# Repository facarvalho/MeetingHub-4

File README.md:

# MeetingHub-4

Analog audio hub for 4 laptops — monitor all four at once (per-source + master
volume), speak on one at a time with a physical mic selector, use one ordinary
TRRS headset, install nothing on any laptop. 100 % analog: no USB audio, no
Bluetooth, no firmware.

## Versions

| | [`v1/`](v1/) — fabricated | [`v2/`](v2/) — respin | [`v3/`](v3/) — mic selector only |
|---|---|---|---|
| Scope | monitor 4 + talk on 1 | monitor 4 + talk on 1 | **talk on 1 only** (audio → external mixer + Y-cables) |
| PCB | 4-layer, 265 × 160 mm | **2-layer**, 192 × 156 mm | **4-layer** (GND + 5 V planes), ~**106 × 86 mm** |
| Assembly | 3 SMD groups + jack SMD pads | **100 % through-hole** | **100 % through-hole** (vertical passives) |
| Mic selector | latching push-locks driving relays | **on-board one-hot latch** (CD4043B + diode matrix + 2N7000), momentary buttons, power-on = muted | **same one-hot latch**; relay NC pulled to GND via 2k2 so a de-selected notebook still reads "mic present" |
| Audio path | mixer + headphone amp + pots + VBIAS | mixer + headphone amp + pots + VBIAS (LM358) | **none** |
| Status | fabricated (JLCPCB lot `W2026080810364558`); first article found 3 schematic bugs | routed, DRC-clean; **not yet fabricated** | routed, DRC-clean, sim 22/22; **not yet fabricated** — open in KiCad, run native ERC/DRC first |

Each folder is **self-contained** (its own `hardware/`, `docs/`, scripts, BOM,
gerbers). Start with the `README.md` / `CLAUDE.md` inside the folder you want.

- **v1 history & rework:** `v1/README.md`, `v1/docs/REWORK-001…004`,
  `v1/docs/Architecture/SCH-010-OneHotMicSelector.md` (the selector design that
  became v2).
- **v2 design & build:** `v2/README.md`, `v2/docs/v2-DESIGN.md`,
  `v2/docs/v1-vs-v2.md`, `v2/CHANGELOG.md`.
- **v3 (mic selector only):** `v3/README.md`, `v3/docs/v3-DESIGN.md`,
  `v3/CHANGELOG.md`.

## License

Commercial license with usage royalty — see [LICENSE.md](LICENSE.md). Not open
hardware; commercial use requires a paid license. No document here is legal
advice.

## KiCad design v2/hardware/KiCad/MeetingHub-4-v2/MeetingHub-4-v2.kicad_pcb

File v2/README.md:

# MeetingHub-4 v2

Analog audio hub for 4 laptops — monitor all four at once, talk on one — with a
single TRRS headset. No drivers, no firmware, 100 % analog.

**v2 = a clean respin of the design:** 2-layer PCB, every part through-hole and
hand-solderable, the mic selector's exclusive "one-hot" logic now on the board
itself, no mute button, and all three bugs from the first fabricated batch fixed.

| | |
|---|---|
| **Status** | Schematic complete, PCB **fully auto-routed** (2 layers, rev-8: 850 seg / 30 vias), DRC clean apart from known cosmetic items. Not yet fabricated. Open in KiCad to tidy silkscreen and run native DRC before ordering. |
| **PCB** | 2 layers, **192 × 156 mm**, R6 rounded corners, 6× M3, GND pour both sides. |
| **Enclosure** | top + bottom acrylic only, sides open (no front panel). |
| **Supply** | USB-C, 5 V only (no regulator, no boost). |
| **BOM** | 117 parts, 100 % THT — every LCSC code in stock with a ready footprint (rev-8 audit). PCBA: [`BOM-PCBA`](hardware/BOM/BOM-PCBA-MeetingHub-4-v2.csv) · upload [`BOM-JLC`](hardware/BOM/BOM-JLC-MeetingHub-4-v2.csv) for assembly · [component photos + links](docs/components.html). |
| **Fab files** | [`hardware/Gerbers/MeetingHub-4-v2-Gerbers.zip`](hardware/Gerbers/) — order as **2-layer**, 1.6 mm, HASL is fine. `…-CPL.csv` has the per-footprint rotation fixes for JLC assembly. |

## How it works

- **Monitor:** each laptop plugs into J2–J5 (TRRS). Its L/R audio goes through a
  DC-block, a per-laptop volume pot (RV1–RV4), a 4-input stereo summing mixer
  (U1 NJM4580), a master volume (RV5), a headphone amp (U2 NJM4556A), out to the
  headset J6. All four are always summed.
- **Talk:** the headset mic (J6 sleeve) is routed by one of four signal relays
  (K1–K4) to exactly one laptop's mic pin.
- **Selecting:** four momentary buttons (SW2–SW5). Press NB2 → laptop 2's relay
  latches on and any other releases (KVM-style). The latch is a CD4043B
  (U4) + diode matrix + 4× 2N7000 coil drivers (the SELECT_LOGIC sheet).
- **Mute:** there is no mute button. **At power-on nothing is latched → the mic
  reaches no laptop → muted.** During a call, mute in the meeting app, or hold
  any two select buttons.
- **Volume direction:** clockwise = louder on every pot (verified against the
  Alps terminal convention — see the design doc).

## Reading order

1. [`docs/v2-DESIGN.md`](docs/v2-DESIGN.md) — what changed from v1, the
   one-hot logic, and the 3-pass circuit review (4 laptops connected).
2. [`CLAUDE.md`](CLAUDE.md) — repo layout and how the files were generated.
3. [`CHANGELOG.md`](CHANGELOG.md).
4. The KiCad project in [`hardware/KiCad/MeetingHub-4-v2/`](hardware/KiCad/MeetingHub-4-v2/).

The v1/v2 design and its hand-rework guides are in the parent folder and are
**not** part of v2.

## License

Inherits the parent project's commercial license with usage royalty — see
`../LICENSE.md`. Not open-source hardware.

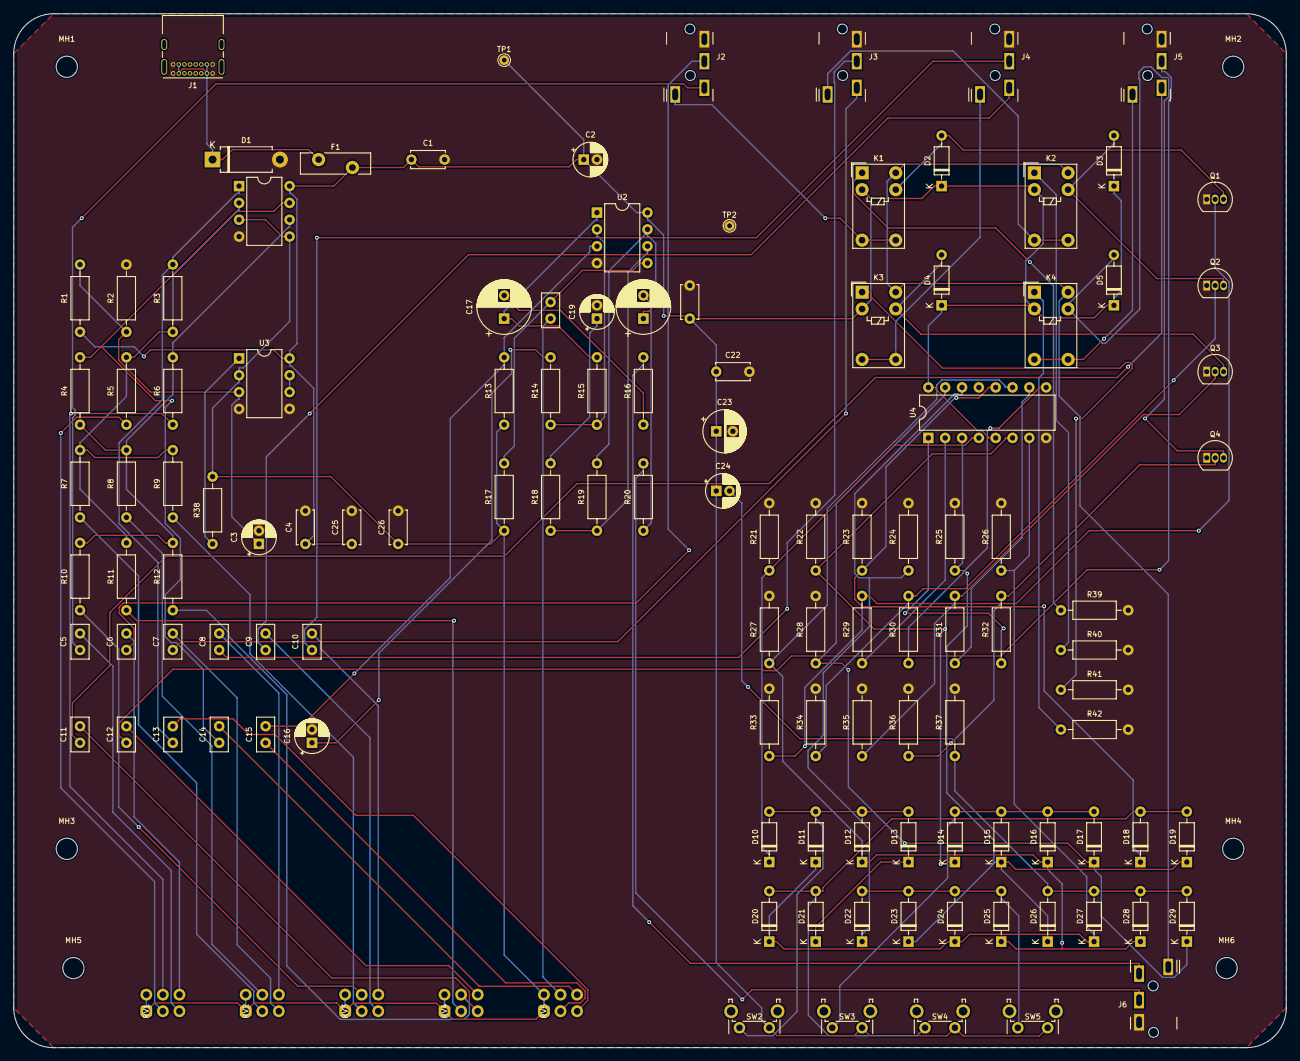
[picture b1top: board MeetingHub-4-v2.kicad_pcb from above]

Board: 2 copper layers, 192.0 x 156.0 mm, 129 parts (0 on the bottom side), 85 nets.

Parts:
C1, C4, C21, C22, C25, C26: C_Disc_D5.0mm_W2.5mm_P5.00mm
C2, C3, C16, C19, C24: CP_Radial_D5.0mm_P2.00mm
C5, C6, C7, C8, C9, C10, C11, C12, C13, C14, C15, C18: C_Disc_D5.0mm_W2.5mm_P2.50mm
C17, C20: CP_Radial_D8.0mm_P3.50mm
C23: CP_Radial_D6.3mm_P2.50mm
D1: D_DO-15_P10.16mm_Horizontal
D2, D3, D4, D5, D10, D11, D12, D13, D14, D15, D16, D17, D18, D19, D20, D21, D22, D23, D24, D25, D26, D27, D28, D29: D_DO-35_SOD27_P7.62mm_Horizontal
F1: Fuse_Bourns_MF-RG500
J1: USB_C_Receptacle_GCT_USB4085
J2, J3, J4, J5, J6: Jack_3.5mm_PJ-3200B-4A_Horizontal
K1, K2, K3, K4: Relay_SPDT_Omron_G5V-1
MH1, MH2, MH3, MH4, MH5, MH6: MountingHole_3.2mm_M3
Q1, Q2, Q3, Q4: TO-92_Inline
R1, R2, R3, R4, R5, R6, R7, R8, R9, R10, R11, R12, R13, R14, R15, R16, R17, R18, R19, R20, R21, R22, R23, R24, R25, R26, R27, R28, R29, R30, R31, R32, R33, R34, R35, R36, R37, R38, R39, R40, R41, R42: R_Axial_DIN0207_L6.3mm_D2.5mm_P10.16mm_Horizontal
RV1, RV2, RV3, RV4, RV5: Potentiometer_Alps_RK097_Dual_Horizontal
SW2, SW3, SW4, SW5: SW_Tactile_SPST_Angled_PTS645Vx39-2LFS
TP1, TP2: TestPoint_THTPad_D1.5mm_Drill0.7mm
U1, U2, U3: DIP-8_W7.62mm
U4: DIP-16_W7.62mm

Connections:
+5V_AUDIO: C1.1, C2.1, C4.1, C21.1, C22.1, C23.1, C24.1, C25.1, D2.1, D3.1, D4.1, D5.1, F1.2, K1.2, K2.2, K3.2, K4.2, R1.1, SW2.1, SW3.1, SW4.1, SW5.1, TP1.1, U1.8, U2.8, U3.8, U4.5, U4.16
/MIC_SWITCHING/NCHLD1: K1.1, R39.1
/MIC_SWITCHING/NCHLD2: K2.1, R40.1
/MIC_SWITCHING/NCHLD3: K3.1, R41.1
/MIC_SWITCHING/NCHLD4: K4.1, R42.1
/SELECT_LOGIC/BTN1: D10.2, D11.2, D12.2, D13.2, SW2.2
/SELECT_LOGIC/BTN2: D14.2, D15.2, D16.2, D17.2, SW3.2
/SELECT_LOGIC/BTN3: D18.2, D19.2, D20.2, D21.2, SW4.2
/SELECT_LOGIC/BTN4: D22.2, D23.2, D24.2, D25.2, SW5.2
/SELECT_LOGIC/GATE1: Q1.2, R29.2, R33.1
/SELECT_LOGIC/GATE2: Q2.2, R30.2, R34.1
/SELECT_LOGIC/GATE3: Q3.2, R31.2, R35.1
/SELECT_LOGIC/GATE4: Q4.2, R32.2, R36.1
/SELECT_LOGIC/PORN: C24.2, D26.2, D27.2, D28.2, D29.2, R37.1
/SELECT_LOGIC/QO1: R29.1, U4.2
/SELECT_LOGIC/QO2: R30.1, U4.9
/SELECT_LOGIC/QO3: R31.1, U4.10
/SELECT_LOGIC/QO4: R32.1, U4.1
/SELECT_LOGIC/RST1: D15.1, D19.1, D23.1, D26.1, R25.1, U4.3
/SELECT_LOGIC/RST2: D11.1, D20.1, D24.1, D27.1, R26.1, U4.7
/SELECT_LOGIC/RST3: D12.1, D16.1, D25.1, D28.1, R27.1, U4.11
/SELECT_LOGIC/RST4: D13.1, D17.1, D21.1, D29.1, R28.1, U4.15
/SELECT_LOGIC/SET1: D10.1, R21.1, U4.4
/SELECT_LOGIC/SET2: D14.1, R22.1, U4.6
/SELECT_LOGIC/SET3: D18.1, R23.1, U4.12
/SELECT_LOGIC/SET4: D22.1, R24.1, U4.14
/SELECT_LOGIC/U3B_FB: U3.6, U3.7
/SELECT_LOGIC/VB_OUT: R38.1, U3.1
COIL1: D2.2, K1.9, Q1.3
COIL2: D3.2, K2.9, Q2.3
COIL3: D4.2, K3.9, Q3.3
COIL4: D5.2, K4.9, Q4.3
GND: C1.2, C2.2, C3.2, C4.2, C16.2, C19.2, C21.2, C22.2, C23.2, C25.2, C26.2, D1.2, J1.A1, J1.A12, J1.B1, J1.B12, J2.R2, J3.R2, J4.R2, J5.R2, J6.R2, Q1.1, Q2.1, Q3.1, Q4.1, R2.2, R21.2, R22.2, R23.2, R24.2, R25.2, R26.2, R27.2, R28.2, R33.2, R34.2, R35.2, R36.2, R37.2, R39.2, R40.2, R41.2, R42.2, TP2.1, U1.4, U2.4, U3.4, U3.5, U4.8
HEADSET_MIC: J6.S, K1.10, K2.10, K3.10, K4.10
MIX_L: C15.1, RV5.2
MIX_R: C18.1, RV5.5
NB1_L: C5.1, J2.T
NB1_MIC: J2.S, K1.5, K1.6
NB1_R: C6.1, J2.R1
NB2_L: C7.1, J3.T
NB2_MIC: J3.S, K2.5, K2.6
NB2_R: C8.1, J3.R1
NB3_L: C9.1, J4.T
NB3_MIC: J4.S, K3.5, K3.6
NB3_R: C10.1, J4.R1
NB4_L: C11.1, J5.T
NB4_MIC: J5.S, K4.5, K4.6
NB4_R: C12.1, J5.R1
unnamed: C5.2, RV1.3
unnamed: C6.2, RV1.6
unnamed: C7.2, RV2.3
unnamed: C8.2, RV2.6
unnamed: C9.2, RV3.3
unnamed: C10.2, RV3.6
unnamed: C11.2, RV4.3
unnamed: C12.2, RV4.6
unnamed: C13.1, R3.2, U1.1
unnamed: C13.2, RV5.3
unnamed: C14.1, R4.2, U1.7
unnamed: C14.2, RV5.6
unnamed: C16.1, R14.2
unnamed: C17.1, R15.2, U2.1
unnamed: C17.2, R16.1
unnamed: C19.1, R18.2
unnamed: C20.1, R19.2, U2.7
unnamed: C20.2, R20.1
unnamed: D1.1, F1.1, J1.A4, J1.A9, J1.B4, J1.B9
unnamed: J6.R1, R20.2
unnamed: J6.T, R16.2
unnamed: R5.1, RV1.2
unnamed: R6.1, RV1.5
unnamed: R7.1, RV2.2
unnamed: R8.1, RV2.5
unnamed: R9.1, RV3.2
unnamed: R10.1, RV3.5
unnamed: R11.1, RV4.2
unnamed: R12.1, RV4.5
unnamed: R3.1, R5.2, R7.2, R9.2, R11.2, U1.2
unnamed: R4.1, R6.2, R8.2, R10.2, R12.2, U1.6
unnamed: C15.2, R13.2, U2.3
unnamed: R14.1, R15.1, U2.2
unnamed: C18.2, R17.2, U2.5
unnamed: R18.1, R19.1, U2.6
VBIAS: C26.1, R13.1, R17.1, R38.2, RV1.1, RV1.4, RV2.1, RV2.4, RV3.1, RV3.4, RV4.1, RV4.4, RV5.1, RV5.4, U1.3, U1.5, U3.2
VBIAS_REF: C3.1, R1.2, R2.1, U3.3

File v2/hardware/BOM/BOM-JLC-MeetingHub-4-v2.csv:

Comment,Designator,Footprint,JLCPCB Part #
K104K15X7RF5TH5,"C1, C4, C21, C22, C25",C_Disc_D5.0mm_P5.00mm,C2167231
KM106M016D11RR0VH2FP0,"C2, C3, C16, C19, C24",CP_Radial_D5.0mm_P2.00mm,C43799
K105K20X7RF5TH5,"C5, C6, C7, C8, C9, C10, C11, C12, C13, C14, C15, C18, C26",C_Disc_D5.0mm_P2.50mm,C2167638
KM227M035F12RR0VH2FP0,"C17, C20",CP_Radial_D8.0mm_P3.50mm,C2063
NXA16V100M5X11,C23,CP_Radial_D6.3mm_P2.50mm,C346930
P6KE6.8A,D1,D_DO-15_P10.16mm,C152132
1N4148,"D2, D3, D4, D5, D10, D11, D12, D13, D14, D15, D16, D17, D18, D19, D20, D21, D22, D23, D24, D25, D26, D27, D28, D29",D_DO-35_P7.62mm,C402212
RXEF050,F1,Fuse_Bourns_MF-RG500,C76399
USB4085-GF-A,J1,USB_C_Receptacle_GCT_USB4085,C7095263
PJ-3200B-4A,"J2, J3, J4, J5, J6",Jack_3.5mm_PJ-3200B-4A_Horizontal,C136687
G5V-1-DC5,"K1, K2, K3, K4",Relay_SPDT_Omron_G5V-1,C28695
2N7000,"Q1, Q2, Q3, Q4",TO-92_Inline,C9114
CFR-25JB-52-10K,"R1, R2, R5, R6, R7, R8, R9, R10, R11, R12",R_Axial_DIN0207_P10.16mm,C5618323
MF1/4W-3.3K-1%,"R3, R4",R_Axial_DIN0207_P10.16mm,C119335
MFR-25FBF52-100K,"R13, R17, R21, R22, R23, R24, R25, R26, R27, R28, R33, R34, R35, R36, R37",R_Axial_DIN0207_P10.16mm,C1364475
CF1/4W-1KR-J,"R14, R15, R18, R19, R29, R30, R31, R32",R_Axial_DIN0207_P10.16mm,C120055
MFR0W4F100JA50,"R16, R20",R_Axial_DIN0207_P10.16mm,C57437
MFR-25FBF52-47R5,R38,R_Axial_DIN0207_P10.16mm,C3373549
CFR-25JB-52-2K2,"R39, R40, R41, R42",R_Axial_DIN0207_P10.16mm,C1364486
RK09712200HA,"RV1, RV2, RV3, RV4, RV5",Potentiometer_Alps_RK097_Dual_Horizontal,C470545
PTS645VK392LFS,"SW2, SW3, SW4, SW5",SW_Tactile_SPST_Angled_PTS645Vx39-2LFS,C285519
NJM4580DD,U1,DIP-8_W7.62mm,C5184871
NJM4556AD,U2,DIP-8_W7.62mm,C2838125
LM358P,U3,DIP-8_W7.62mm,C5213
CD4043BE,U4,DIP-16_W7.62mm,C22390239

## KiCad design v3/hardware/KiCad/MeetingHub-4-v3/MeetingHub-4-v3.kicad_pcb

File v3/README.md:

# MeetingHub-4 v3 — Mic Selector

A stripped-down spin of MeetingHub-4: **only the microphone selector**. One
headset microphone is routed to **exactly one** of four notebooks, KVM-style,
with four buttons. There is **no audio/monitor path** — you split each notebook
with a TRRS Y-cable and monitor all four on an external mixer.

|  |  |
|---|---|
| **Status** | Schematic complete, PCB routed (4 layers, 0 unrouted), DRC clean (0 errors, 1 cosmetic silk item). **Simulated with the real parts in ngspice: 25 / 25**, plus a 22 / 22 analytic cross-check (`docs/v3-simulation-validation.md`). **Not fabricated.** Open in KiCad, run native ERC/DRC before ordering. |
| **PCB** | **4 layers** (F/B signal, In1 = GND plane, In2 = +5V plane), ~**106 × 86 mm** (≈ ⅓ the area of v2), R3 corners, 4× M3. |
| **Supply** | USB-C, 5 V only (PTC fuse + TVS, CC pull-downs so any USB-C source turns VBUS on). |
| **BOM** | ~73 parts, **100 % through-hole**, hand-solderable. Vertical-mount resistors/diodes keep it small. |
| **Fab files** | `hardware/Gerbers/` (order **4-layer**, 1.6 mm) + `…-CPL.csv`. |

## How it works

- **Route:** the headset mic (`J6` tip) goes to the **NO** contact of all four
  signal relays `K1–K4`, commoned. Each relay's **COM** goes to one notebook's
  mic jack (`J2–J5`); its **NC** goes through a 2.2 kΩ resistor (`R20–R23`) to
  ground. Energise `Kn` → notebook *n* gets the headset mic. De-energise it →
  that notebook's mic pin sees 2.2 kΩ to ground (~1.1 V), which a laptop codec
  reads as *"headset mic present, silent"* — **not** an open circuit, which many
  codecs read as *"mic unplugged"* and then fall back to the notebook's internal
  mic (transmitting room audio). See `docs/v3-simulation-validation.md` MIC7.
- **Select:** four momentary buttons `SW1–SW4`. Press NB2 → `K2` latches on and
  any other relay drops (exclusive / one-hot). The latch is a **CD4043B** quad
  NOR R/S latch (`U1`) + a 16-diode steering matrix + `2N7000` coil drivers —
  the exact logic proven in v2's simulation.
- **Mute:** there is no mute button. **At power-on nothing is latched → the mic
  reaches no notebook → muted.** A ~0.1 s power-on-reset pulse (`C5`/`R11` +
  `D22–D25`) guarantees this even on a slow VBUS ramp. During a call, mute in
  the meeting app, or hold any two select buttons. In every muted state each
  notebook still sees the 2.2 kΩ NC bias, so none of them report the mic gone.

## The rest of your setup (not on this board)

```
notebook 3.5 mm combo jack ──[ TRRS Y-splitter ]──┬── headphone plug ──► external mixer
                                                  └── mic plug ────────► MeetingHub-4 v3  Jn
headset ──┬── headphones ──► external mixer
          └── mic plug ─────► MeetingHub-4 v3  J6
```

All five jacks (`J2–J6`) are **P2 (3.5 mm) 3-conductor through-hole** — HX
PJ-320A-3P DIP, **LCSC C17701689**. The footprint pins are numbered **2 / 3 / 4**
per the datasheet: **pin 3 = tip → mic, pins 2 & 4 = ring/sleeve → ground**
(a CTIA Y-splitter's mic plug puts the mic on the tip and grounds the rest;
grounding both 2 and 4 also means it doesn't matter which is ring and which is
sleeve). On bring-up, meter continuity from a plug's tip to **pin 3** to confirm.
Power the board from a **separate** USB charger or power bank (not one of the
four notebooks) so the notebooks' audio grounds don't form a loop through the box.

## Reading order

1. [`docs/v3-DESIGN.md`](docs/v3-DESIGN.md) — what was kept from v2, what was
   dropped, the one-hot logic, and the circuit review.
2. [`docs/v3-simulation-validation.md`](docs/v3-simulation-validation.md) — the
   ngspice component-level simulation (25 checks) + the analytic cross-check.
3. [`CLAUDE.md`](CLAUDE.md) — repo layout and how the files are generated.
4. [`CHANGELOG.md`](CHANGELOG.md).
5. The KiCad project in [`hardware/KiCad/MeetingHub-4-v3/`](hardware/KiCad/MeetingHub-4-v3/).

## License

Inherits the parent project's commercial license with usage royalty — see
`../LICENSE.md`. Not open-source hardware.

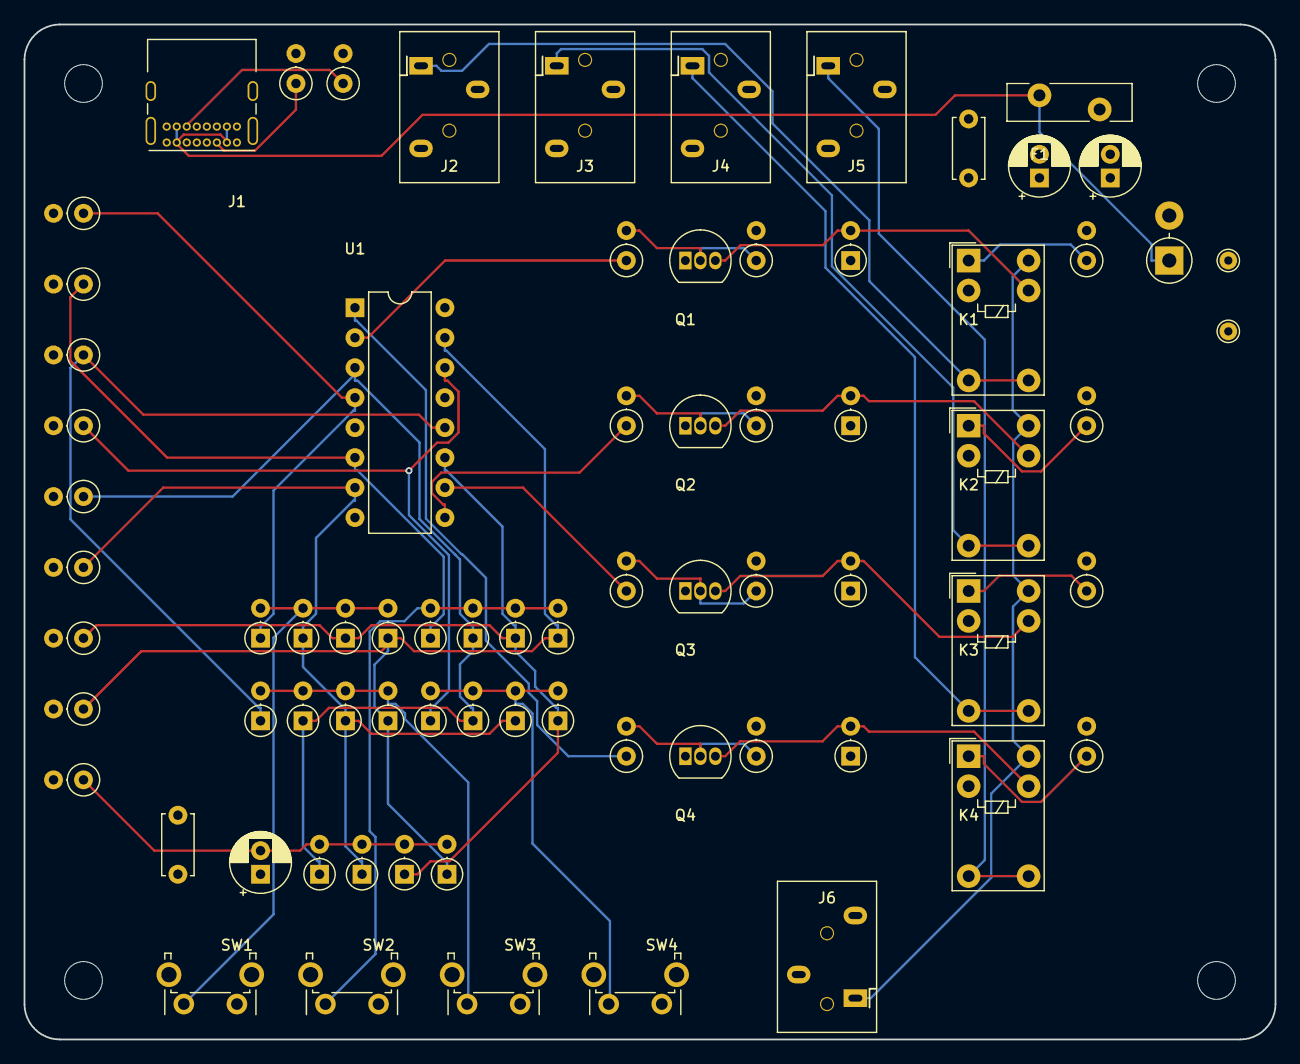
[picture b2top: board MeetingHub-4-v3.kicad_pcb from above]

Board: 4 copper layers, 106.0 x 86.0 mm, 79 parts (0 on the bottom side), 39 nets.

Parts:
C1, C4: C_Disc_D5.0mm_W2.5mm_P5.00mm
C2, C3, C5: CP_Radial_D5.0mm_P2.00mm
D1: D_DO-15_P3.81mm_Vertical_AnodeUp
D2, D3, D4, D5, D6, D7, D8, D9, D10, D11, D12, D13, D14, D15, D16, D17, D18, D19, D20, D21, D22, D23, D24, D25: D_DO-35_SOD27_P2.54mm_Vertical_AnodeUp
F1: Fuse_Bourns_MF-RG500
J1: USB_C_Receptacle_GCT_USB4085
J2, J3, J4, J5, J6: Jack_3.5mm_3pole_THT_Horizontal
K1, K2, K3, K4: Relay_SPDT_Omron_G5V-1
MH1, MH2, MH3, MH4: MountingHole_3.2mm_M3
Q1, Q2, Q3, Q4: TO-92_Inline
R1, R2, R3, R4, R5, R6, R7, R8, R9, R10, R11, R12, R13, R14, R15, R16, R17, R18, R19, R20, R21, R22, R23: R_Axial_DIN0207_L6.3mm_D2.5mm_P2.54mm_Vertical
SW1, SW2, SW3, SW4: SW_Tactile_SPST_Angled_PTS645Vx39-2LFS
TP1, TP2: TestPoint_THTPad_D1.5mm_Drill0.7mm
U1: DIP-16_W7.62mm

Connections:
+5V: C1.1, C2.1, C3.1, C4.1, C5.1, D2.1, D3.1, D4.1, D5.1, F1.2, K1.2, K2.2, K3.2, K4.2, SW1.1, SW2.1, SW3.1, SW4.1, TP1.1, U1.5, U1.16
/BTN1: D6.2, D7.2, D8.2, D9.2, SW1.2
/BTN2: D10.2, D11.2, D12.2, D13.2, SW2.2
/BTN3: D14.2, D15.2, D16.2, D17.2, SW3.2
/BTN4: D18.2, D19.2, D20.2, D21.2, SW4.2
/CC1: J1.A5, R1.1
/CC2: J1.B5, R2.1
/COIL1: D2.2, K1.9, Q1.3
/COIL2: D3.2, K2.9, Q2.3
/COIL3: D4.2, K3.9, Q3.3
/COIL4: D5.2, K4.9, Q4.3
/GATE1: Q1.2, R12.2, R16.1
/GATE2: Q2.2, R13.2, R17.1
/GATE3: Q3.2, R14.2, R18.1
/GATE4: Q4.2, R15.2, R19.1
/NCBIAS1: K1.1, R20.1
/NCBIAS2: K2.1, R21.1
/NCBIAS3: K3.1, R22.1
/NCBIAS4: K4.1, R23.1
/PORN: C5.2, D22.2, D23.2, D24.2, D25.2, R11.1
/QO1: R12.1, U1.2
/QO2: R13.1, U1.9
/QO3: R14.1, U1.10
/QO4: R15.1, U1.1
/RST1: D11.1, D15.1, D19.1, D22.1, R7.1, U1.3
/RST2: D7.1, D16.1, D20.1, D23.1, R8.1, U1.7
/RST3: D8.1, D12.1, D21.1, D24.1, R9.1, U1.11
/RST4: D9.1, D13.1, D17.1, D25.1, R10.1, U1.15
/SET1: D6.1, R3.1, U1.4
/SET2: D10.1, R4.1, U1.6
/SET3: D14.1, R5.1, U1.12
/SET4: D18.1, R6.1, U1.14
/VBUS: D1.1, F1.1, J1.A4, J1.A9, J1.B4, J1.B9
GND: C1.2, C2.2, C3.2, C4.2, D1.2, J1.A1, J1.A12, J1.B1, J1.B12, J1.S1, J2.2, J2.4, J3.2, J3.4, J4.2, J4.4, J5.2, J5.4, J6.2, J6.4, Q1.1, Q2.1, Q3.1, Q4.1, R1.2, R2.2, R3.2, R4.2, R5.2, R6.2, R7.2, R8.2, R9.2, R10.2, R11.2, R16.2, R17.2, R18.2, R19.2, R20.2, R21.2, R22.2, R23.2, TP2.1, U1.8
HS_MIC: J6.3, K1.10, K2.10, K3.10, K4.10
NB1_MIC: J2.3, K1.5, K1.6
NB2_MIC: J3.3, K2.5, K2.6
NB3_MIC: J4.3, K3.5, K3.6
NB4_MIC: J5.3, K4.5, K4.6

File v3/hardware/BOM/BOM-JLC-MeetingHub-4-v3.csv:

Comment,Designator,Footprint,JLCPCB Part #
K104K15X7RF5TH5,"C1, C4",C_Disc_D5.0mm_P5.00mm,C2167231
KM106M016D11RR0VH2FP0,"C2, C5",CP_Radial_D5.0mm_P2.00mm,C43799
KM476M016C11RR0VH3FP0,C3,CP_Radial_D5.0mm_P2.00mm,C177036
P6KE6.8A,D1,D_DO-15_P3.81mm,C152132
1N4148,"D2, D3, D4, D5, D6, D7, D8, D9, D10, D11, D12, D13, D14, D15, D16, D17, D18, D19, D20, D21, D22, D23, D24, D25",D_DO-35_P2.54mm,C402212
RXEF050,F1,Fuse_Bourns_MF-RG500,C76399
USB4085-GF-A,J1,USB_C_Receptacle_GCT_USB4085,C7095263
PJ-320A-3P DIP,"J2, J3, J4, J5, J6",Jack_3.5mm_3pole_THT_Horizontal,C17701689
G5V-1-DC5,"K1, K2, K3, K4",Relay_SPDT_Omron_G5V-1,C28695
2N7000,"Q1, Q2, Q3, Q4",TO-92_Inline,C9114
CFR0W4J0512A50,"R1, R2",R_Axial_DIN0207_P2.54mm_Vertical,C22962
MFR-25FBF52-100K,"R3, R4, R5, R6, R7, R8, R9, R10, R11, R16, R17, R18, R19",R_Axial_DIN0207_P2.54mm_Vertical,C1364475
CF1/4W-1KR-J,"R12, R13, R14, R15",R_Axial_DIN0207_P2.54mm_Vertical,C120055
CFR0W4J0222A50,"R20, R21, R22, R23",R_Axial_DIN0207_P2.54mm_Vertical,C22975
PTS645VK392LFS,"SW1, SW2, SW3, SW4",SW_Tactile_SPST_Angled_PTS645Vx39-2LFS,C285519
CD4043BE,U1,DIP-16_W7.62mm,C22390239

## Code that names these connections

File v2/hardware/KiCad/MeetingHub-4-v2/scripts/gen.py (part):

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s.connect(ux,uy,CD_PINS,"16","+5V_AUDIO",glob=True)
s.connect(ux,uy,CD_PINS,"8","GND",glob=True)
s.connect(ux,uy,CD_PINS,"5","+5V_AUDIO",glob=True)      # ENABLE
s.connect(ux,uy,CD_PINS,"4","SET1"); s.connect(ux,uy,CD_PINS,"3","RST1")
s.connect(ux,uy,CD_PINS,"6","SET2"); s.connect(ux,uy,CD_PINS,"7","RST2")
s.connect(ux,uy,CD_PINS,"12","SET3");s.connect(ux,uy,CD_PINS,"11","RST3")
s.connect(ux,uy,CD_PINS,"14","SET4");s.connect(ux,uy,CD_PINS,"15","RST4")
s.connect(ux,uy,CD_PINS,"2","QO1"); s.connect(ux,uy,CD_PINS,"9","QO2")
s.connect(ux,uy,CD_PINS,"10","QO3");s.connect(ux,uy,CD_PINS,"1","QO4")
s.nc(ux,uy,CD_PINS,"13")
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# ---- power-on reset : +5V -C24- PORN -R37- GND ; PORN -> D26..29 -> RST1..4 ----
# C24 = 10uF electrolytic (was 1uF): stretches the reset window to ~40ms so a
# slow USB-C VBUS ramp still guarantees Q1..Q4 = 0 (mic muted) at power-on.
# Polarity: pin1(+) -> +5V, pin2(-) -> PORN (PORN never rises above +5V).
s.sym("Device:C_Polarized","C24","10uF",40,150,FP_CP5,["1","2"])
s.connect(40,150,C_PINS,"1","+5V_AUDIO",glob=True)
s.connect(40,150,C_PINS,"2","PORN")
s.sym("Device:R","R37","100k",40,168,FP_R,["1","2"])
s.connect(40,168,R_PINS,"1","PORN")
s.connect(40,168,R_PINS,"2","GND",glob=True)
for j,line in enumerate(["RST1","RST2","RST3","RST4"]):
    x,y = 58, 140+j*8
    s.sym("Device:D", f"D{26+j}", "1N4148", x, y, FP_D, ["1","2"])
    s.connect(x,y,D_PINS,"2","PORN")     # anode -> PORN
    s.connect(x,y,D_PINS,"1",line)       # cathode -> RST line

# ---- MOSFET coil drivers Q1..Q4 : QOn -R(1k)- GATEn -R(100k)- GND ; Q.G=GATEn Q.S=GND Q.D=COILn
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# exact and the 1uF load cap can't destabilise the LM358.
bx,by = 250, 70
s.sym("Amplifier_Operational:LM2904","U3","LM358",bx,by,FP_DIP8,["1","2","3"],unit=1)
s.connect(bx,by,OP_PINS,"3","VBIAS_REF",glob=True)
s.connect(bx,by,OP_PINS,"1","VB_OUT")
s.connect(bx,by,OP_PINS,"2","VBIAS",glob=True)
s.sym("Device:R","R38","47R",268,70,FP_R,["1","2"])
s.connect(268,70,R_PINS,"1","VB_OUT")
s.connect(268,70,R_PINS,"2","VBIAS",glob=True)
# unit 3 (power)
s.sym("Amplifier_Operational:LM2904","U3","LM358",bx,by-40,FP_DIP8,["4","8"],unit=3)
s.connect(bx,by-40,OP_PINS,"8","+5V_AUDIO",glob=True)
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# unit 2 (spare) : +in -> GND, -in -> out (follower), out only to its own -in
s.sym("Amplifier_Operational:LM2904","U3","LM358",bx,by+40,FP_DIP8,["5","6","7"],unit=2)
s.connect(bx,by+40,OP_PINS,"5","GND",glob=True)
s.connect(bx,by+40,OP_PINS,"6","U3B_FB")
s.connect(bx,by+40,OP_PINS,"7","U3B_FB")
# C25 opamp decap, C26 VBIAS bulk
s.sym("Device:C","C25","100nF",285,45,FP_C,["1","2"])
s.connect(285,45,C_PINS,"1","+5V_AUDIO",glob=True)
s.connect(285,45,C_PINS,"2","GND",glob=True)
s.sym("Device:C","C26","1uF",285,95,FP_C,["1","2"])
s.connect(285,95,C_PINS,"1","VBIAS",glob=True)
s.connect(285,95,C_PINS,"2","GND",glob=True)

# assemble lib_symbols for SELECT_LOGIC
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    m.connect(kx,ky,K_PINS,"9",f"COIL{n}",glob=True)
    m.connect(kx,ky,K_PINS,"5",f"NB{n}_MIC",glob=True)     # COM -> laptop n
    m.connect(kx,ky,K_PINS,"6",f"NB{n}_MIC",glob=True)     # COM -> laptop n
    m.connect(kx,ky,K_PINS,"10","HEADSET_MIC",glob=True)   # NO  -> headset electret
    m.connect(kx,ky,K_PINS,"1",f"NCHLD{n}")                # NC  -> hold-up resistor
    # de-selected hold-up resistor R39..R42 : NC -> 2k2 -> GND
    rx,ry = 70, 40+(n-1)*40 - 8
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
